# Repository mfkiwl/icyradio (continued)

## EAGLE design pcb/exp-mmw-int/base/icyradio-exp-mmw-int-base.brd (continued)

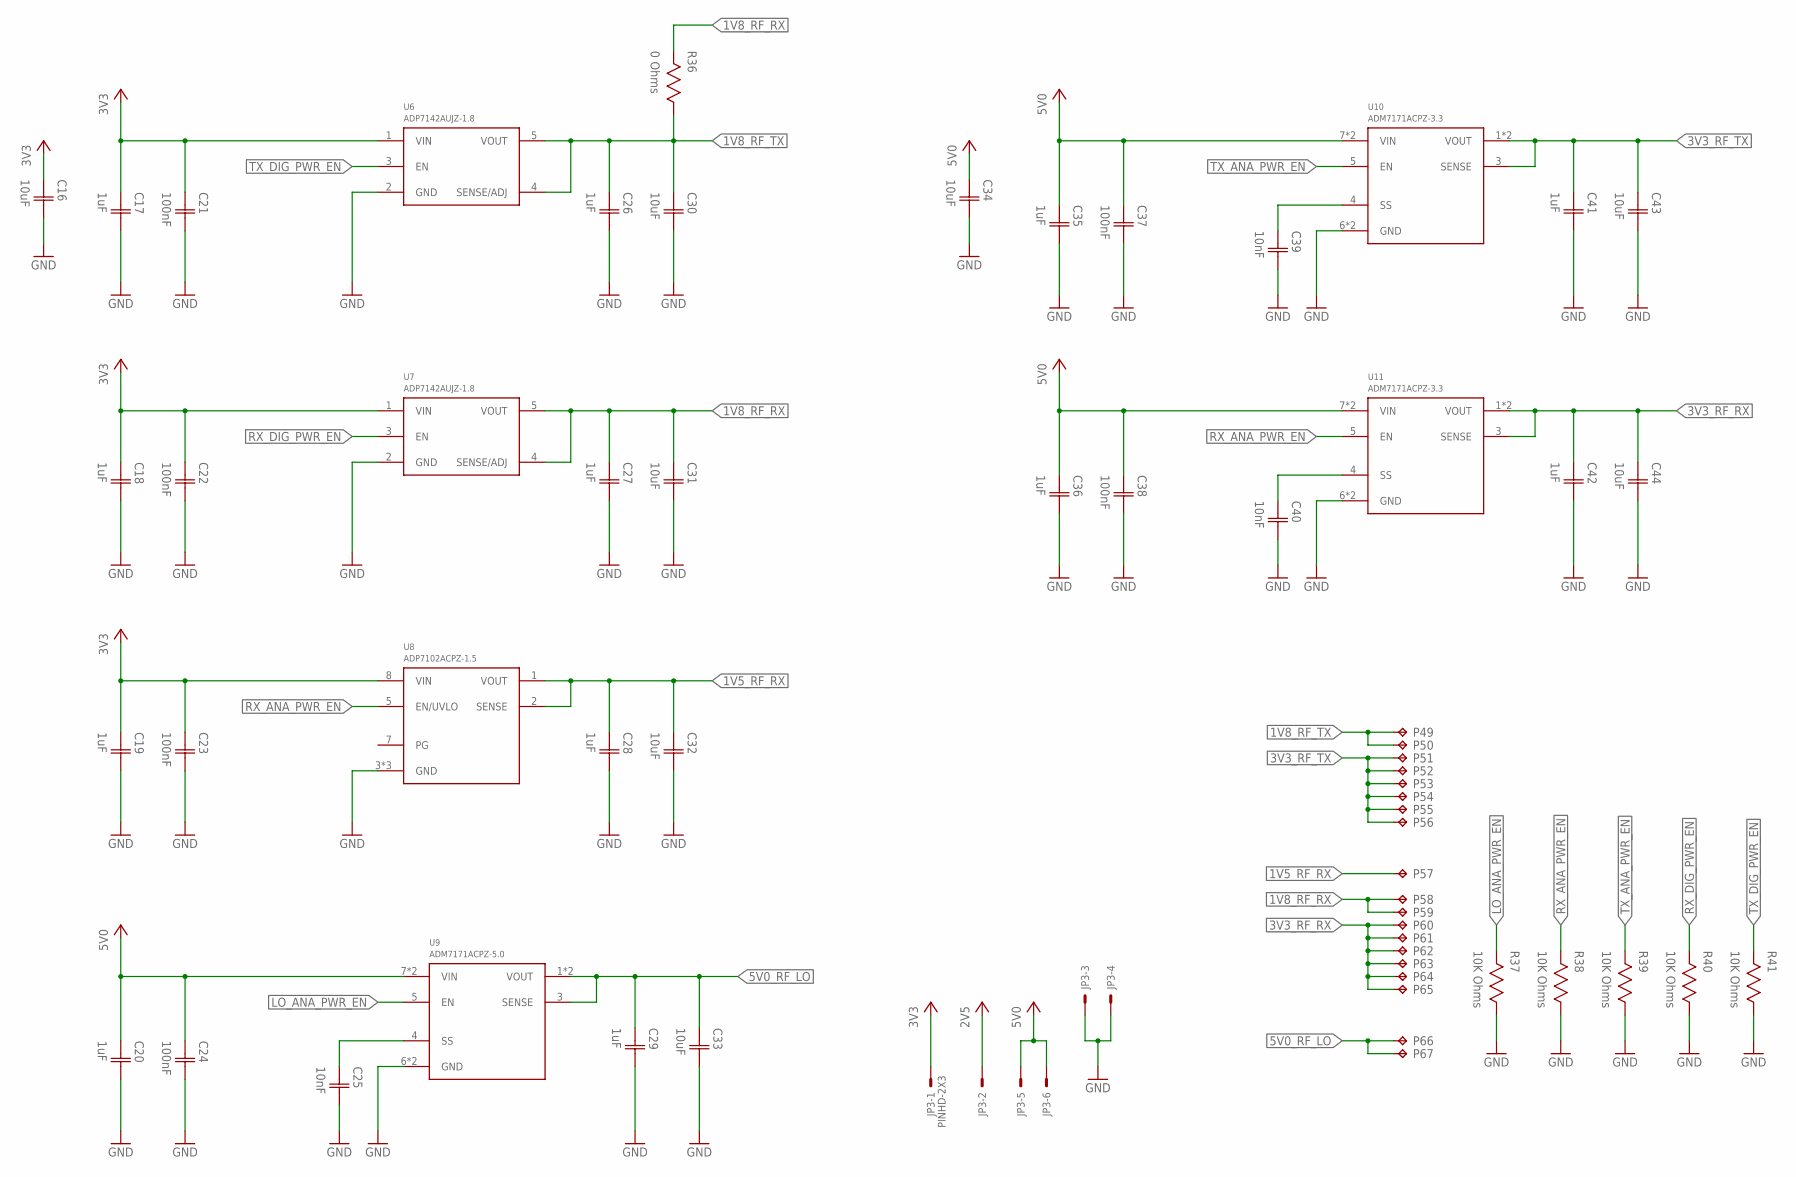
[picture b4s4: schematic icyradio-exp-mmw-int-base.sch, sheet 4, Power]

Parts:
C16, C34: 10uF; CAP0603
C17, C18, C19, C20, C26, C27, C28, C29, C35, C36, C41, C42: 1uF; CAP0402
C21, C22, C23, C24, C37, C38: 100nF; CAP0402
C25, C39, C40: 10nF; CAP0402
C30, C31, C32, C33, C43, C44: 10uF; CAP0402
JP3: PINHD-2X3; 2X03
P49, P50, P51, P52, P53, P54, P55, P56, P57, P58, P59, P60, P61, P62, P63, P64, P65, P66, P67: CHOLE-0.9MM-LAND; CAST_HOLE_0P9MM_LAND
R36: 0 Ohms; RES0402
R37, R38, R39, R40, R41: 10K Ohms; RES0402
U6, U7: ADP7142AUJZ-1.8; SOT23-5
U8: ADP7102ACPZ-1.5; LFCSP8_3X3
U9: ADM7171ACPZ-5.0; LFCSP8_3X3
U10, U11: ADM7171ACPZ-3.3; LFCSP8_3X3

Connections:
1V5_RF_RX: C28.1 (C1), C32.1 (C1), P57.PAD_T, U8.1 (VOUT), U8.2 (SENSE)
1V8_RF_RX: C27.1 (C1), C31.1 (C1), P58.PAD_T, P59.PAD_T, R36.2, U7.4 (SENSE/ADJ), U7.5 (VOUT); also elsewhere on the board
1V8_RF_TX: C26.1 (C1), C30.1 (C1), P49.PAD_T, P50.PAD_T, R36.1, U6.4 (SENSE/ADJ), U6.5 (VOUT); also elsewhere on the board
2V5: JP3.2
3V3: C16.1 (C1), C17.1 (C1), C18.1 (C1), C19.1 (C1), C21.1 (C1), C22.1 (C1), C23.1 (C1), JP3.1, U6.1 (VIN), U7.1 (VIN), U8.8 (VIN); also elsewhere on the board
3V3_RF_RX: C42.1 (C1), C44.1 (C1), P60.PAD_T, P61.PAD_T, P62.PAD_T, P63.PAD_T, P64.PAD_T, P65.PAD_T, U11.1 (VOUT), U11.2 (VOUT), U11.3 (SENSE)
3V3_RF_TX: C41.1 (C1), C43.1 (C1), P51.PAD_T, P52.PAD_T, P53.PAD_T, P54.PAD_T, P55.PAD_T, P56.PAD_T, U10.1 (VOUT), U10.2 (VOUT), U10.3 (SENSE)
5V0: C20.1 (C1), C24.1 (C1), C34.1 (C1), C35.1 (C1), C36.1 (C1), C37.1 (C1), C38.1 (C1), JP3.5, JP3.6, U9.7 (VIN), U9.8 (VIN), U10.7 (VIN), U10.8 (VIN), U11.7 (VIN), U11.8 (VIN)
5V0_RF_LO: C29.1 (C1), C33.1 (C1), P66.PAD_T, P67.PAD_T, U9.1 (VOUT), U9.2 (VOUT), U9.3 (SENSE)
GND: C16.2 (C2), C17.2 (C2), C18.2 (C2), C19.2 (C2), C20.2 (C2), C21.2 (C2), C22.2 (C2), C23.2 (C2), C24.2 (C2), C25.2 (C2), C26.2 (C2), C27.2 (C2), C28.2 (C2), C29.2 (C2), C30.2 (C2), C31.2 (C2), C32.2 (C2), C33.2 (C2), C34.2 (C2), C35.2 (C2), C36.2 (C2), C37.2 (C2), C38.2 (C2), C39.2 (C2), C40.2 (C2), C41.2 (C2), C42.2 (C2), C43.2 (C2), C44.2 (C2), JP3.3, JP3.4, R37.1, R38.1, R39.1, R40.1, R41.1, U6.2 (GND), U7.2 (GND), U8.3 (GND), U8.6 (GND), U8.9 (GND), U9.6 (GND), U9.9 (GND), U10.6 (GND), U10.9 (GND), U11.6 (GND), U11.9 (GND); also elsewhere on the board
LO_ANA_PWR_EN: R37.2, U9.5 (EN); also elsewhere on the board
unnamed: C40.1 (C1), U11.4 (SS)
unnamed: C25.1 (C1), U9.4 (SS)
unnamed: C39.1 (C1), U10.4 (SS)
RX_ANA_PWR_EN: R38.2, U8.5 (EN/UVLO), U11.5 (EN); also elsewhere on the board
RX_DIG_PWR_EN: R40.2, U7.3 (EN); also elsewhere on the board
TX_ANA_PWR_EN: R39.2, U10.5 (EN); also elsewhere on the board
TX_DIG_PWR_EN: R41.2, U6.3 (EN); also elsewhere on the board

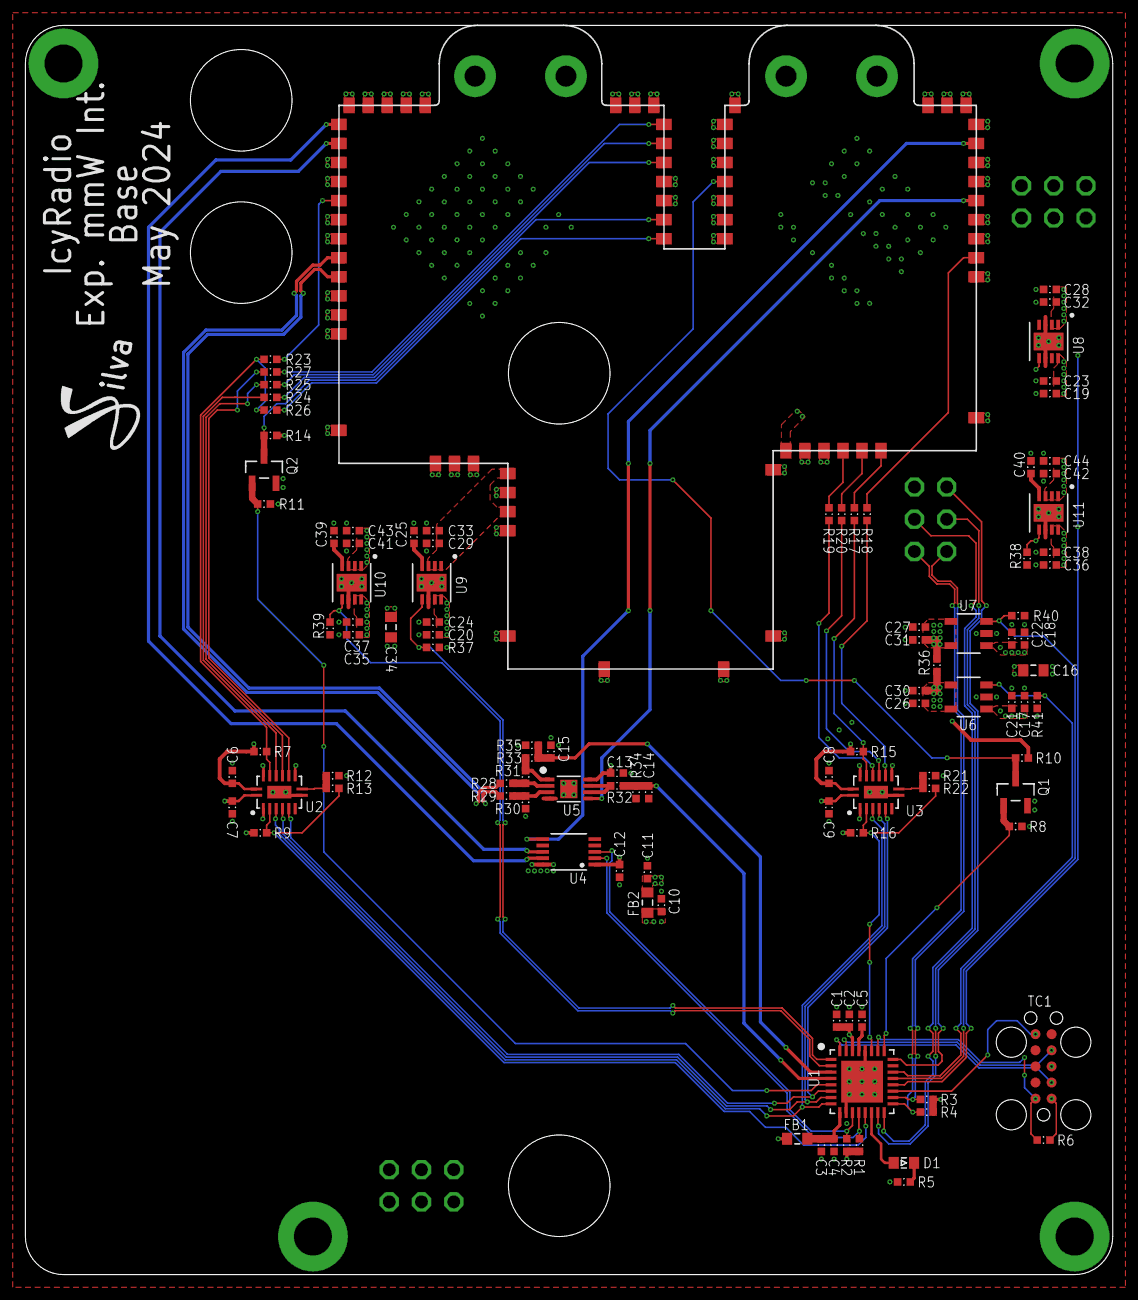
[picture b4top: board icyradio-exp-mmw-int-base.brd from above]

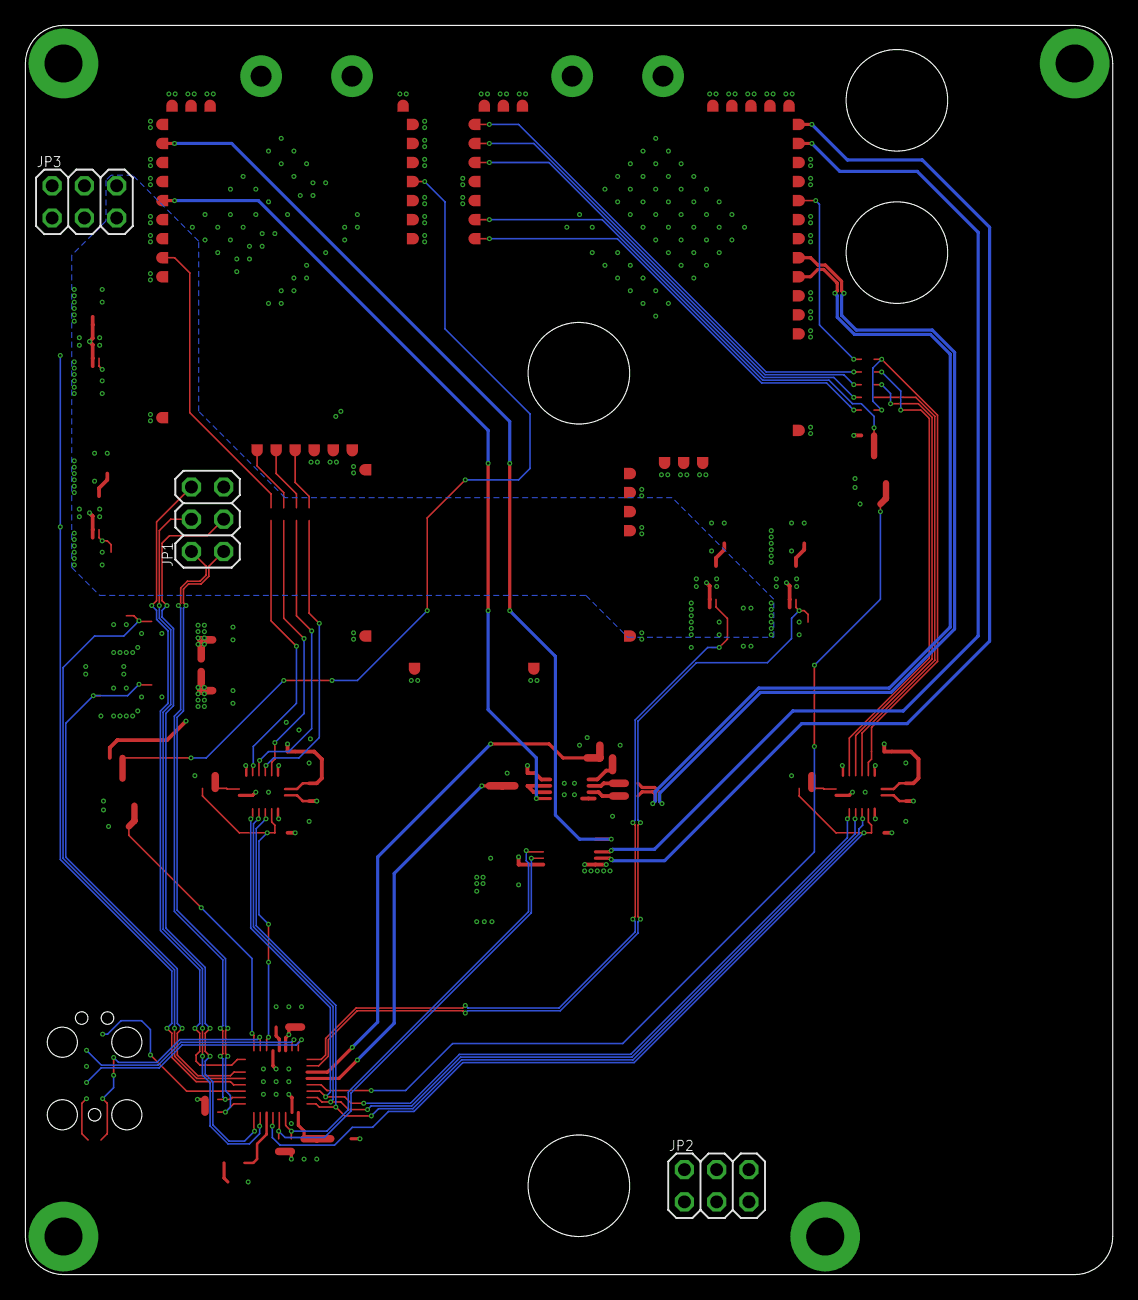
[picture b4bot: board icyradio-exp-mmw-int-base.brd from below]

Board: 4 copper layers, 85.7 x 98.4 mm, 173 parts (3 on the bottom side), 73 nets.

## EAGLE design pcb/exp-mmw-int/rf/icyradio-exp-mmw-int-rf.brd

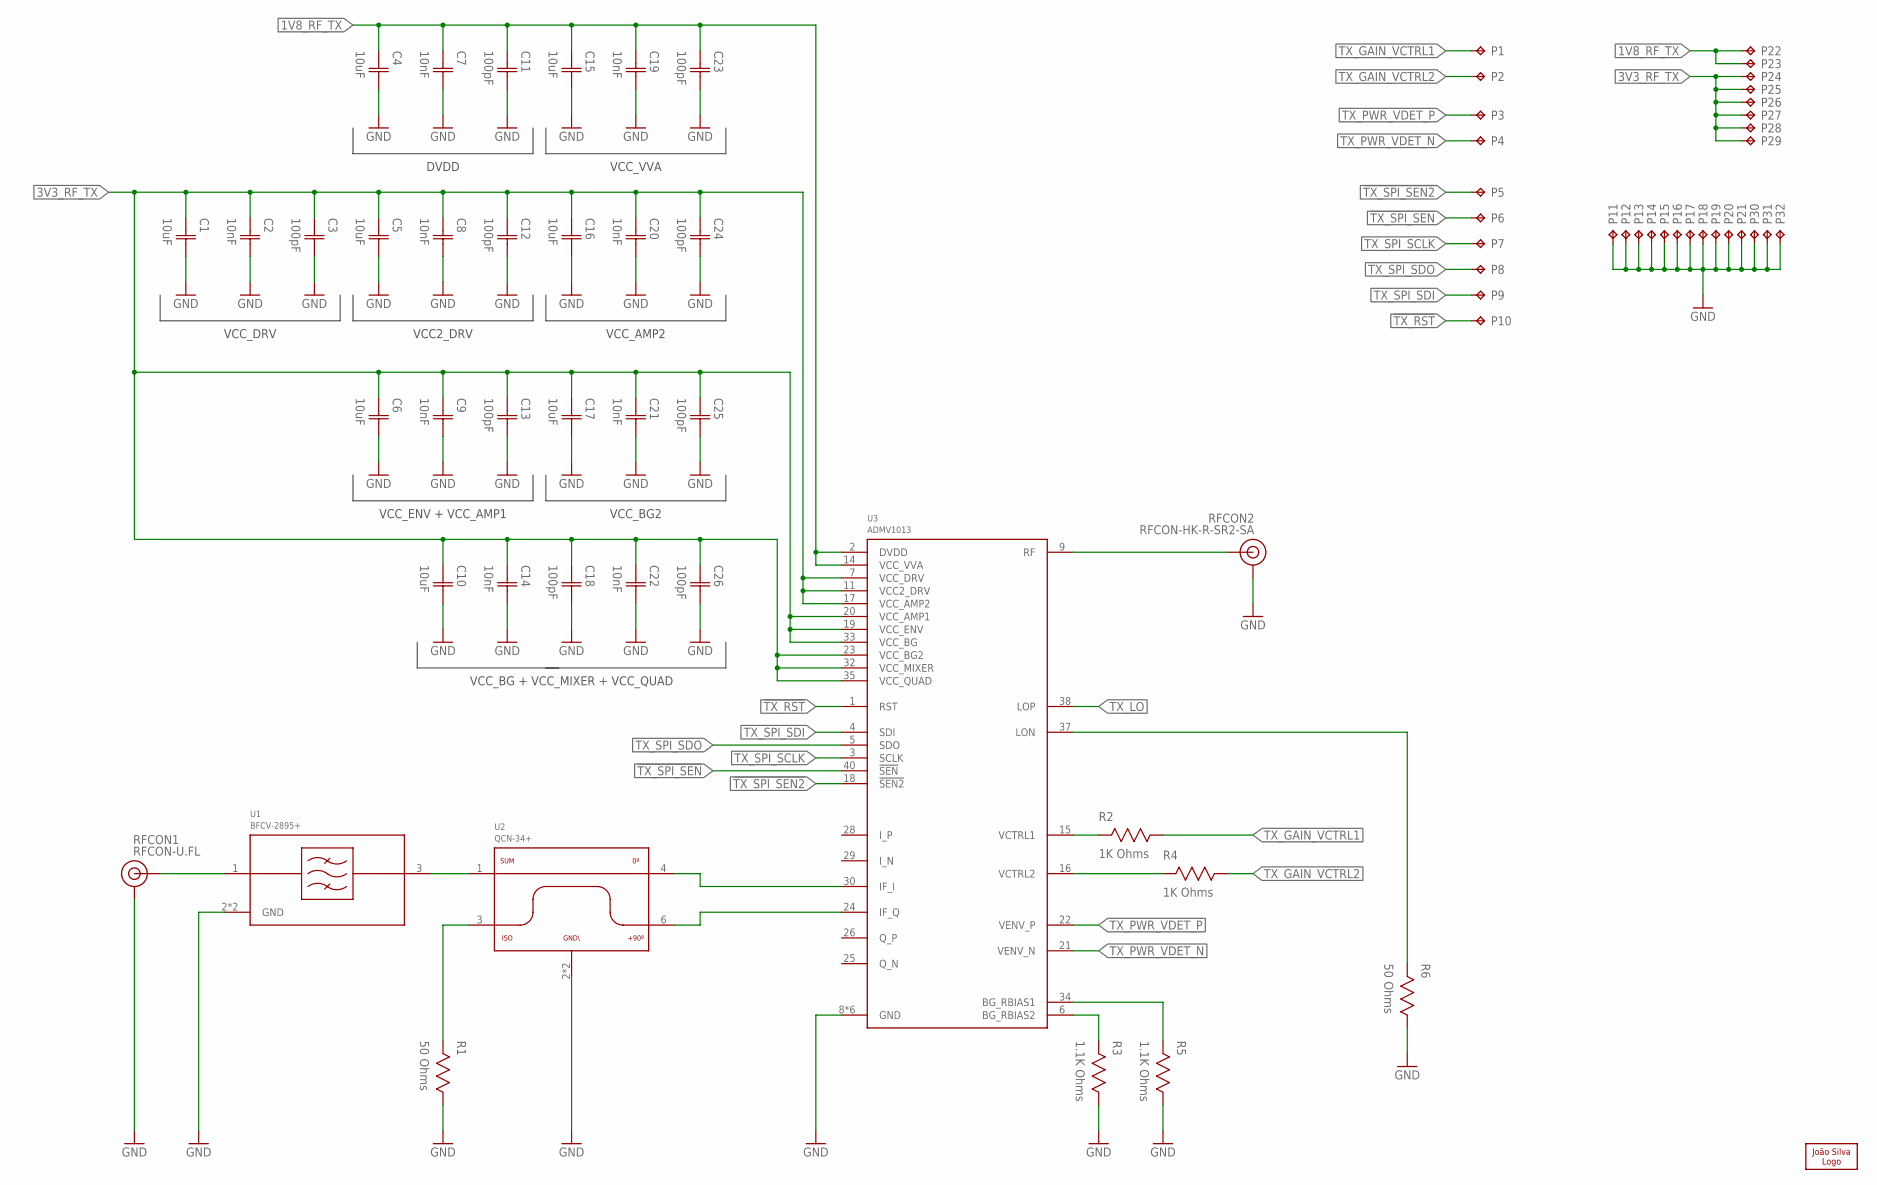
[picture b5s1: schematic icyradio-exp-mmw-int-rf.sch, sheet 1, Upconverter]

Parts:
C1, C4, C5, C6, C10, C15, C16, C17: 10uF; CAP0402
C2, C7, C8, C9, C14, C19, C20, C21, C22: 10nF; CAP0402
C3, C11, C12, C13, C18, C23, C24, C25, C26: 100pF; CAP0402
LOGO1: JSILVA-5MM; JSILVA_5MM
P1, P2, P3, P4, P5, P6, P7, P8, P9, P10, P22, P23, P24, P25, P26, P27, P28, P29: CHOLE-0.9MM-SS; CAST_HOLE_0P9MM_SS
P11, P12, P13, P14, P15, P16, P17, P18, P19, P20, P21, P30, P31, P32: CHOLE-0.9MM-DS; CAST_HOLE_0P9MM_DS
R1, R6: 50 Ohms; RES0402
R2, R4: 1K Ohms; RES0402
R3, R5: 1.1K Ohms; RES0402
RFCON1: RFCON-U.FL; U.FL
RFCON2: RFCON-HK-R-SR2-SA; HK-R-SR2-SA
U1: BFCV-2895+; JV1210C
U2: QCN-34+; FV1206-1
U3: ADMV1013; LGA40

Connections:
1V8_RF_TX: C4.1 (C1), C7.1 (C1), C11.1 (C1), C15.1 (C1), C19.1 (C1), C23.1 (C1), P22.PAD_T, P23.PAD_T, U3.2 (DVDD), U3.14 (VCC_VVA)
3V3_RF_TX: C1.1 (C1), C2.1 (C1), C3.1 (C1), C5.1 (C1), C6.1 (C1), C8.1 (C1), C9.1 (C1), C10.1 (C1), C12.1 (C1), C13.1 (C1), C14.1 (C1), C16.1 (C1), C17.1 (C1), C18.1 (C1), C20.1 (C1), C21.1 (C1), C22.1 (C1), C24.1 (C1), C25.1 (C1), C26.1 (C1), P24.PAD_T, P25.PAD_T, P26.PAD_T, P27.PAD_T, P28.PAD_T, P29.PAD_T, U3.7 (VCC_DRV), U3.11 (VCC2_DRV), U3.17 (VCC_AMP2), U3.19 (VCC_ENV), U3.20 (VCC_AMP1), U3.23 (VCC_BG2), U3.32 (VCC_MIXER), U3.33 (VCC_BG), U3.35 (VCC_QUAD)
!TX_RST: P10.PAD_T, U3.1 (RST)
!TX_SPI_SEN: P6.PAD_T, U3.40 (!SEN)
!TX_SPI_SEN2: P5.PAD_T, U3.18 (!SEN2)
GND: C1.2 (C2), C2.2 (C2), C3.2 (C2), C4.2 (C2), C5.2 (C2), C6.2 (C2), C7.2 (C2), C8.2 (C2), C9.2 (C2), C10.2 (C2), C11.2 (C2), C12.2 (C2), C13.2 (C2), C14.2 (C2), C15.2 (C2), C16.2 (C2), C17.2 (C2), C18.2 (C2), C19.2 (C2), C20.2 (C2), C21.2 (C2), C22.2 (C2), C23.2 (C2), C24.2 (C2), C25.2 (C2), C26.2 (C2), P11.PAD_B, P11.PAD_T, P12.PAD_B, P12.PAD_T, P13.PAD_B, P13.PAD_T, P14.PAD_B, P14.PAD_T, P15.PAD_B, P15.PAD_T, P16.PAD_B, P16.PAD_T, P17.PAD_B, P17.PAD_T, P18.PAD_B, P18.PAD_T, P19.PAD_B, P19.PAD_T, P20.PAD_B, P20.PAD_T, P21.PAD_B, P21.PAD_T, P30.PAD_B, P30.PAD_T, P31.PAD_B, P31.PAD_T, P32.PAD_B, P32.PAD_T, R1.1, R3.1, R5.1, R6.1, RFCON1.P$1 (GND), RFCON1.P$2 (GND), RFCON2.GND@1 (GND), RFCON2.GND@2 (GND), U1.2 (GND), U1.4 (GND), U2.2 (GND), U2.5 (GND), U3.8 (GND), U3.10 (GND), U3.27 (GND), U3.36 (GND), U3.39 (GND), U3.41 (GND); also elsewhere on the board
unnamed: R3.2, U3.6 (BG_RBIAS2)
unnamed: R5.2, U3.34 (BG_RBIAS1)
unnamed: R1.2, U2.3 (ISO)
unnamed: R2.2, U3.15 (VCTRL1)
unnamed: R4.2, U3.16 (VCTRL2)
TX_GAIN_VCTRL1: P1.PAD_T, R2.1
TX_GAIN_VCTRL2: P2.PAD_T, R4.1
TX_IF_FILT: U1.3 (RFOUT), U2.1 (SUM)
TX_IF_I: U2.4 (0DEG), U3.30 (IF_I)
TX_IF_IN: RFCON1.P$3 (SIGNAL), U1.1 (RFIN)
TX_IF_Q: U2.6 (P90DEG), U3.24 (IF_Q)
TX_LO: U3.38 (LOP); also elsewhere on the board
TX_LO_N: R6.2, U3.37 (LON)
TX_PWR_VDET_N: P4.PAD_T, U3.21 (VENV_N)
TX_PWR_VDET_P: P3.PAD_T, U3.22 (VENV_P)
TX_RF: RFCON2.SIG (SIGNAL), U3.9 (RF)
TX_SPI_SCLK: P7.PAD_T, U3.3 (SCLK)
TX_SPI_SDI: P9.PAD_T, U3.4 (SDI)
TX_SPI_SDO: P8.PAD_T, U3.5 (SDO)

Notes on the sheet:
DVDD
VCC_VVA
VCC2_DRV
VCC_AMP2
VCC_DRV
VCC_BG2
VCC_ENV + VCC_AMP1
VCC_BG + VCC_MIXER + VCC_QUAD

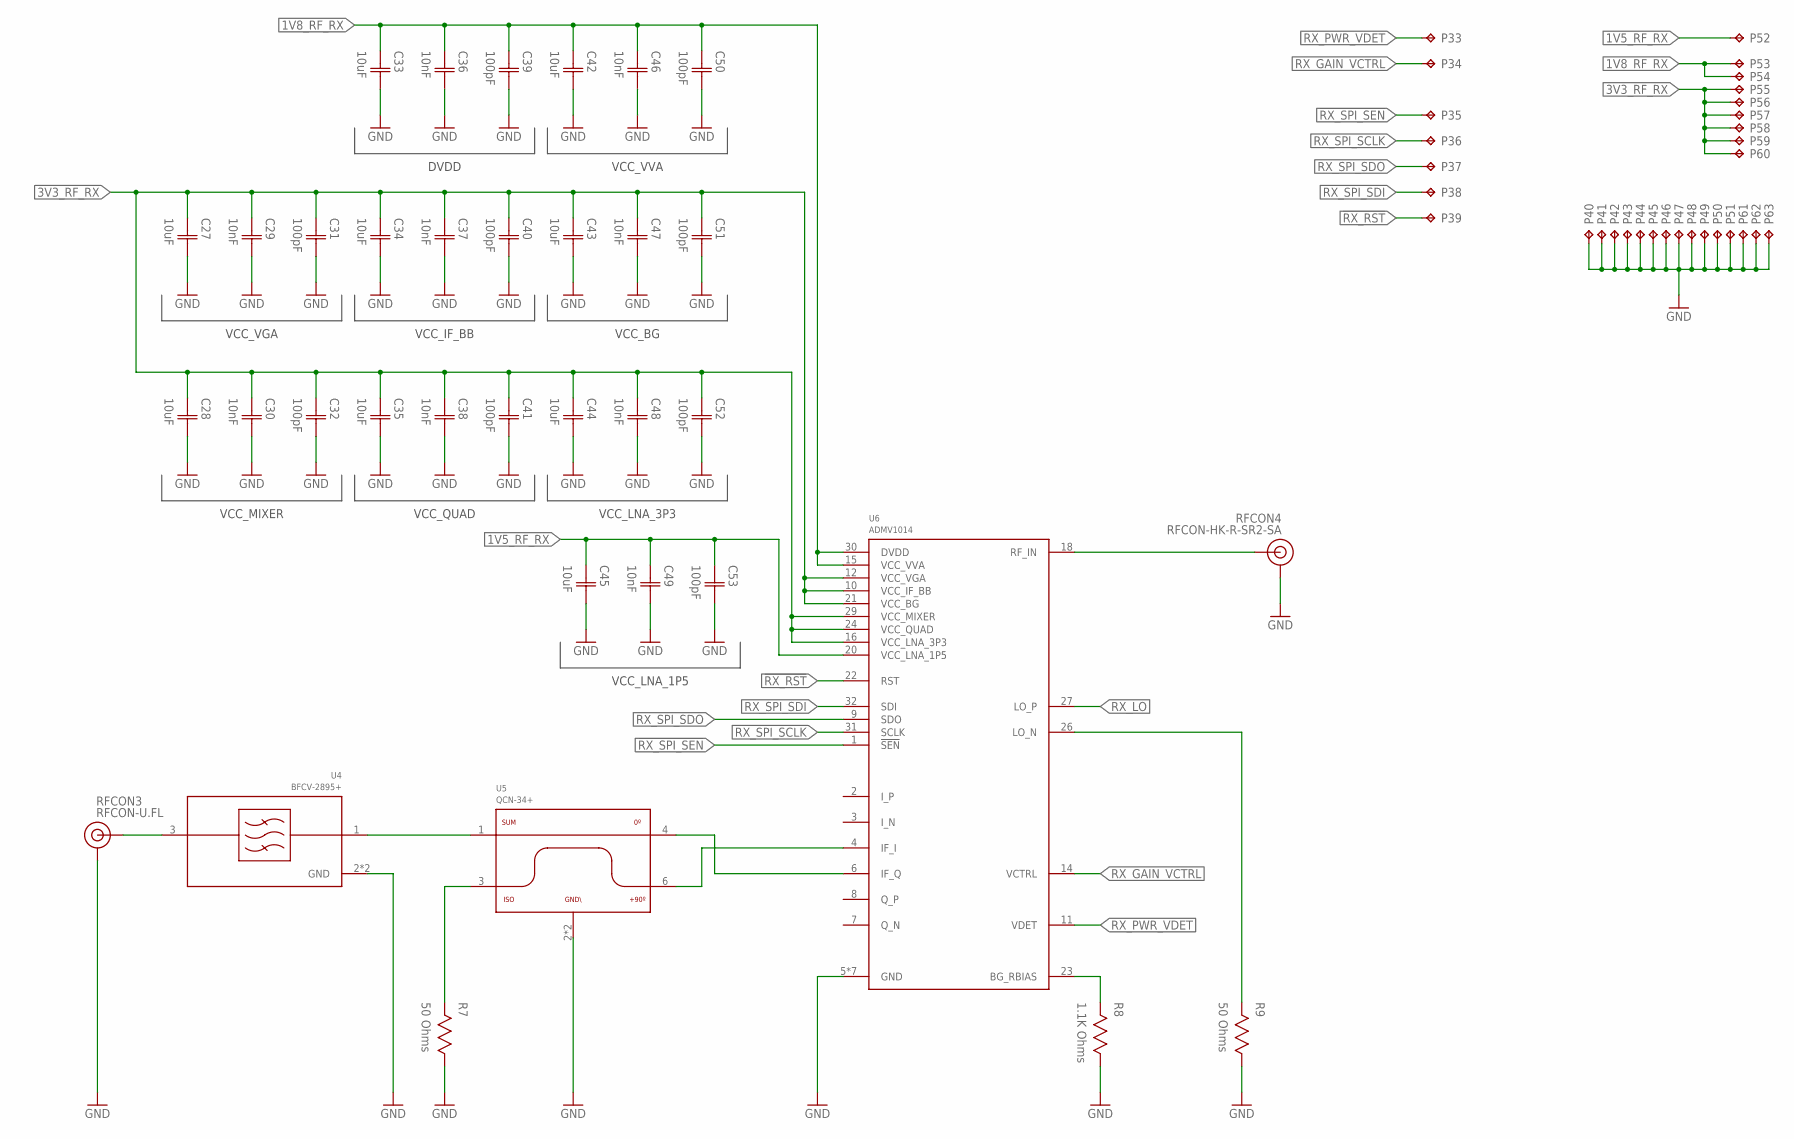
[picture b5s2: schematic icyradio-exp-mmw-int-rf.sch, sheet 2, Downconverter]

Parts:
C27, C28, C33, C34, C35, C42, C43, C44, C45: 10uF; CAP0402
C29, C30, C36, C37, C38, C46, C47, C48, C49: 10nF; CAP0402
C31, C32, C39, C40, C41, C50, C51, C52, C53: 100pF; CAP0402
P33, P34, P35, P36, P37, P38, P39, P52, P53, P54, P55, P56, P57, P58, P59, P60: CHOLE-0.9MM-SS; CAST_HOLE_0P9MM_SS
P40, P41, P42, P43, P44, P45, P46, P47, P48, P49, P50, P51, P61, P62, P63: CHOLE-0.9MM-DS; CAST_HOLE_0P9MM_DS
R7, R9: 50 Ohms; RES0402
R8: 1.1K Ohms; RES0402
RFCON3: RFCON-U.FL; U.FL
RFCON4: RFCON-HK-R-SR2-SA; HK-R-SR2-SA
U4: BFCV-2895+; JV1210C
U5: QCN-34+; FV1206-1
U6: ADMV1014; LGA32

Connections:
1V5_RF_RX: C45.1 (C1), C49.1 (C1), C53.1 (C1), P52.PAD_T, U6.20 (VCC_LNA_1P5)
1V8_RF_RX: C33.1 (C1), C36.1 (C1), C39.1 (C1), C42.1 (C1), C46.1 (C1), C50.1 (C1), P53.PAD_T, P54.PAD_T, U6.15 (VCC_VVA), U6.30 (DVDD)
3V3_RF_RX: C27.1 (C1), C28.1 (C1), C29.1 (C1), C30.1 (C1), C31.1 (C1), C32.1 (C1), C34.1 (C1), C35.1 (C1), C37.1 (C1), C38.1 (C1), C40.1 (C1), C41.1 (C1), C43.1 (C1), C44.1 (C1), C47.1 (C1), C48.1 (C1), C51.1 (C1), C52.1 (C1), P55.PAD_T, P56.PAD_T, P57.PAD_T, P58.PAD_T, P59.PAD_T, P60.PAD_T, U6.10 (VCC_IF_BB), U6.12 (VCC_VGA), U6.16 (VCC_LNA_3P3), U6.21 (VCC_BG), U6.24 (VCC_QUAD), U6.29 (VCC_MIXER)
!RX_RST: P39.PAD_T, U6.22 (RST)
!RX_SPI_SEN: P35.PAD_T, U6.1 (!SEN)
GND: C27.2 (C2), C28.2 (C2), C29.2 (C2), C30.2 (C2), C31.2 (C2), C32.2 (C2), C33.2 (C2), C34.2 (C2), C35.2 (C2), C36.2 (C2), C37.2 (C2), C38.2 (C2), C39.2 (C2), C40.2 (C2), C41.2 (C2), C42.2 (C2), C43.2 (C2), C44.2 (C2), C45.2 (C2), C46.2 (C2), C47.2 (C2), C48.2 (C2), C49.2 (C2), C50.2 (C2), C51.2 (C2), C52.2 (C2), C53.2 (C2), P40.PAD_B, P40.PAD_T, P41.PAD_B, P41.PAD_T, P42.PAD_B, P42.PAD_T, P43.PAD_B, P43.PAD_T, P44.PAD_B, P44.PAD_T, P45.PAD_B, P45.PAD_T, P46.PAD_B, P46.PAD_T, P47.PAD_B, P47.PAD_T, P48.PAD_B, P48.PAD_T, P49.PAD_B, P49.PAD_T, P50.PAD_B, P50.PAD_T, P51.PAD_B, P51.PAD_T, P61.PAD_B, P61.PAD_T, P62.PAD_B, P62.PAD_T, P63.PAD_B, P63.PAD_T, R7.1, R8.1, R9.1, RFCON3.P$1 (GND), RFCON3.P$2 (GND), RFCON4.GND@1 (GND), RFCON4.GND@2 (GND), U4.2 (GND), U4.4 (GND), U5.2 (GND), U5.5 (GND), U6.5 (GND), U6.13 (GND), U6.17 (GND), U6.19 (GND), U6.25 (GND), U6.28 (GND), U6.33 (GND); also elsewhere on the board
unnamed: R8.2, U6.23 (BG_RBIAS)
unnamed: R7.2, U5.3 (ISO)
RX_GAIN_VCTRL: P34.PAD_T, U6.14 (VCTRL)
RX_IF: U4.1 (RFIN), U5.1 (SUM)
RX_IF_FILT: RFCON3.P$3 (SIGNAL), U4.3 (RFOUT)
RX_IF_I: U5.6 (P90DEG), U6.4 (IF_I)
RX_IF_Q: U5.4 (0DEG), U6.6 (IF_Q)
RX_LO: U6.27 (LO_P); also elsewhere on the board
RX_LO_N: R9.2, U6.26 (LO_N)
RX_PWR_VDET: P33.PAD_T, U6.11 (VDET)
RX_RF: RFCON4.SIG (SIGNAL), U6.18 (RF_IN)
RX_SPI_SCLK: P36.PAD_T, U6.31 (SCLK)
RX_SPI_SDI: P38.PAD_T, U6.32 (SDI)
RX_SPI_SDO: P37.PAD_T, U6.9 (SDO)

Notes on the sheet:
DVDD
VCC_VVA
VCC_BG
VCC_VGA
VCC_IF_BB
VCC_LNA_3P3
VCC_QUAD
VCC_LNA_1P5
VCC_MIXER

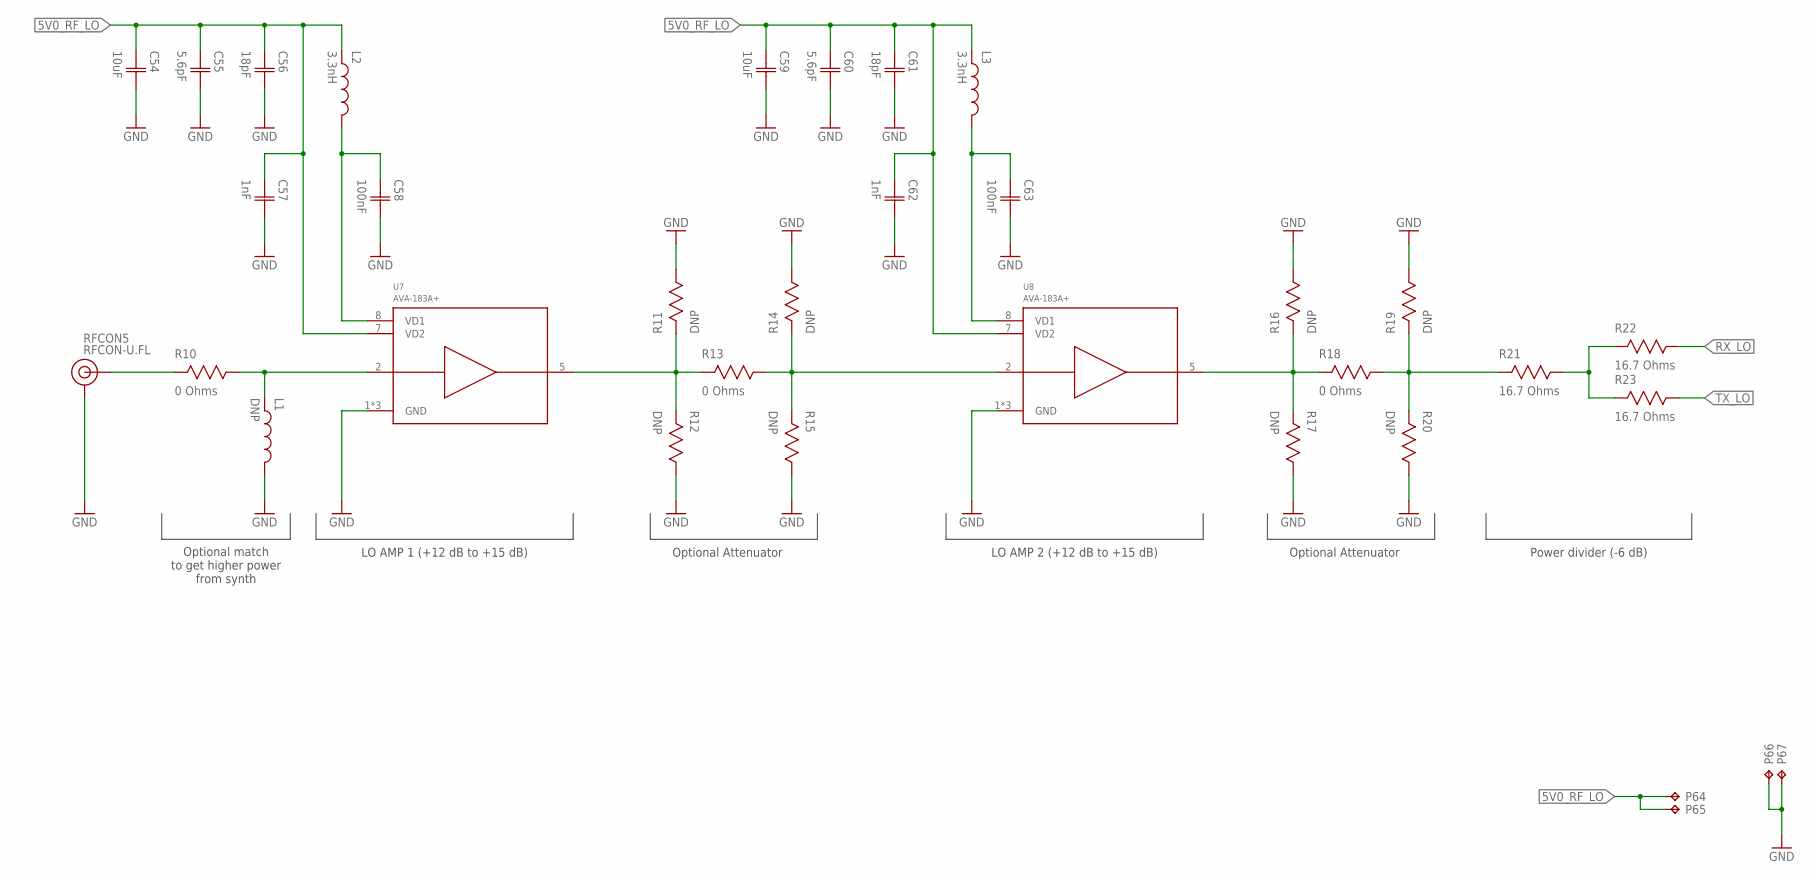
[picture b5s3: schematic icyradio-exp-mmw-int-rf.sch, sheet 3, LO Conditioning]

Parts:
C54, C59: 10uF; CAP0402
C55, C60: 5.6pF; CAP0402
C56, C61: 18pF; CAP0402
C57, C62: 1nF; CAP0402
C58, C63: 100nF; CAP0402
L1: DNP; IND0402
L2, L3: 3.3nH; IND0402
P64, P65: CHOLE-0.9MM-SS; CAST_HOLE_0P9MM_SS
P66, P67: CHOLE-0.9MM-DS; CAST_HOLE_0P9MM_DS
R10, R13, R18: 0 Ohms; RES0402
R11, R12, R14, R15, R16, R17, R19, R20: DNP; RES0402
R21, R22, R23: 16.7 Ohms; RES0402
RFCON5: RFCON-U.FL; U.FL
U7, U8: AVA-183A+; DQ849

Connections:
5V0_RF_LO: C54.1 (C1), C55.1 (C1), C56.1 (C1), C57.1 (C1), C59.1 (C1), C60.1 (C1), C61.1 (C1), C62.1 (C1), L2.1, L3.1, P64.PAD_T, P65.PAD_T, U7.7 (VD2), U8.7 (VD2)
GND: C54.2 (C2), C55.2 (C2), C56.2 (C2), C57.2 (C2), C58.2 (C2), C59.2 (C2), C60.2 (C2), C61.2 (C2), C62.2 (C2), C63.2 (C2), L1.2, P66.PAD_B, P66.PAD_T, P67.PAD_B, P67.PAD_T, R11.1, R12.1, R14.1, R15.1, R16.1, R17.1, R19.1, R20.1, RFCON5.P$1 (GND), RFCON5.P$2 (GND), U7.1 (GND), U7.6 (GND), U7.9 (GND), U8.1 (GND), U8.6 (GND), U8.9 (GND); also elsewhere on the board
LO_AMP1_IN: L1.1, R10.1, U7.2 (RFIN)
LO_AMP1_OUT: R11.2, R12.2, R13.2, U7.5 (RFOUT)
LO_AMP2_IN: R13.1, R14.2, R15.2, U8.2 (RFIN)
LO_AMP2_OUT: R16.2, R17.2, R18.2, U8.5 (RFOUT)
LO_AMP_VD1: C58.1 (C1), L2.2, U7.8 (VD1)
LO_AMP_VD2: C63.1 (C1), L3.2, U8.8 (VD1)
LO_IN: R10.2, RFCON5.P$3 (SIGNAL)
LO_OUT: R18.1, R19.2, R20.2, R21.2
LO_SPLIT: R21.1, R22.2, R23.2
RX_LO: R22.1; also elsewhere on the board
TX_LO: R23.1; also elsewhere on the board

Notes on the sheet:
Optional Attenuator
LO AMP 1 (+12 dB to +15 dB)
LO AMP 2 (+12 dB to +15 dB)
Optional match to get higher power from synth
Power divider (-6 dB)

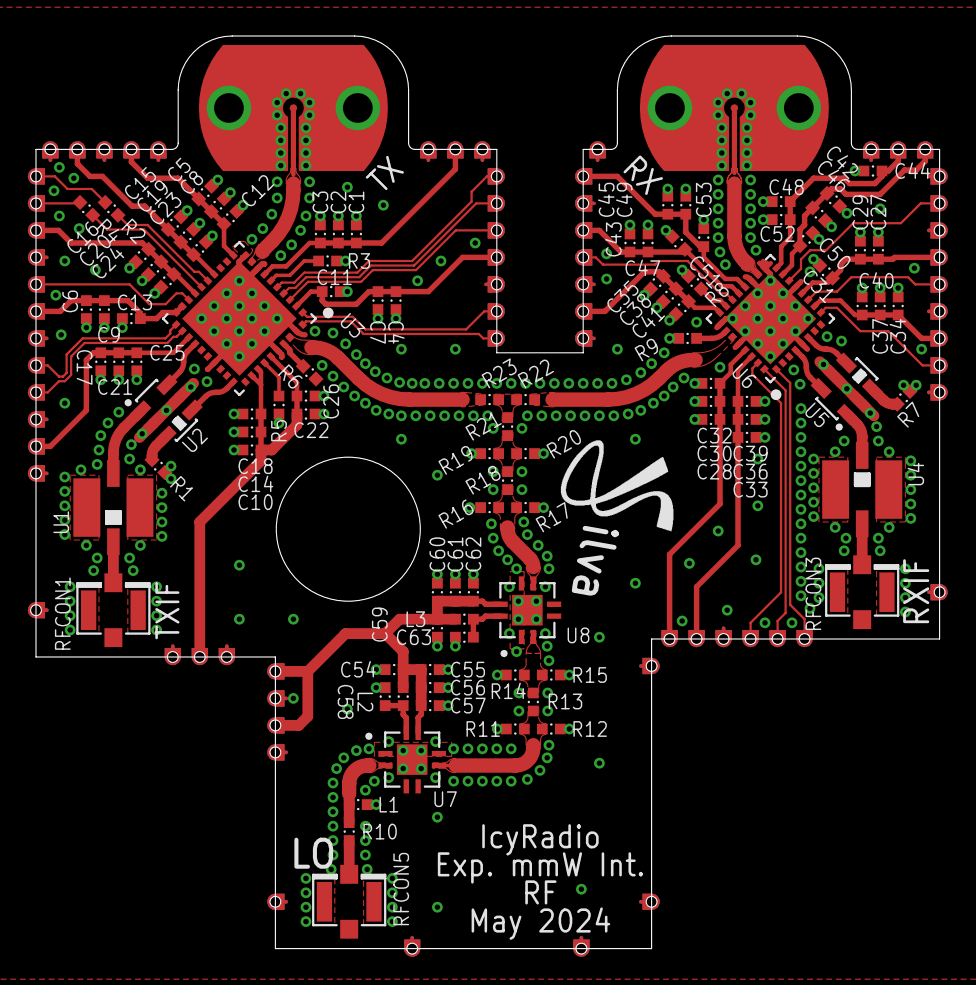
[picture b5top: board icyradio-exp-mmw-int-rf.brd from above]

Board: 2 copper layers, 50.2 x 50.7 mm, 170 parts (0 on the bottom side), 54 nets.

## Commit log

2024-04-06 Start working on mmWave expansion card
2024-04-06 HDL Work
2024-04-06 Add documentation
2024-04-06 driver: Use dma_mmap_coherent on all platforms
2024-04-06 soapy: Fix AD9361 error message soapy: Tune AD9361 to ISM band on startup soapy: Set AD9361 TX attenuation higher on startup soapy: Set AD9361 gain mode to manual on startup soapy: Round I2S clock di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
2024-04-24 soapy: Use 39 MHz as transceiver reference frequency to achieve integer division soapy: Use std::this_thread::sleep_for instead of usleep soapy: Allow 122.88 MSPS overclock sampling soapy: Add loop f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
2024-04-24 pcb: Update 3V3 switching regulator inductor to 4.7 uH so it exits DCM pcb: Update transceiver clock DC-block capacitor to 100nF
2024-04-24 driver: Add DKMS make target
2024-04-24 pmc: Dummy ADC read on startup pmc: Disable floating point ADC read functions at compile time pmc: Fix signed/unsigned integer temperature compensation pmc: Remove floating point math from SERCOM fun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
2024-05-28 firmware: Add Artix 200T project
2024-05-30 Add icyradio-apps repository URL
2024-05-30 pcb: Change mmWave Synth loop filter component values
2024-05-30 pcb: Finish mmWave integrated expansion PCBs for production
2024-05-30 exp/mmw-int: Add firmware
2024-05-30 pmc: Prepare LT7182S library conversion to fixed point pmc: Add fault log management methods (WIP) pmc: Fix unsigned temperature measurement errors pmc: Add debugger presence check pmc: Fix ID typo p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
2024-05-30 exp/template: Copy framework changes from pmc (check previous commits) exp/template: Completely remove floating-point math
2024-05-30 soapy: Explicitly set debug and release build flags soapy: Implement AD9361 gain mode switch methods soapy: Implement AD9361 RSSI readout methods soapy: Implement AD9361 FIR configuration methods soa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
2024-05-30 workflows: Build MCU firmwares in release mode Fix typo templace -> template
2024-06-01 pmc: Completely remove floating point math
2024-06-01 driver: Support multiple DMA buffers driver: Change ioctl calls
2024-06-01 soapy: Use std functions in LT7182S soapy: Check DDR3 init and calibration soapy: Use new ioctl numbers soapy: Start new DMA buffer management implementation soapy: Move utility functions soapy: Misc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
2024-06-05 Update github workflows to assess warnings
2024-06-05 exp-mmw: Work on software
2024-06-06 driver: Use correct DMA flags
2024-06-10 cli: Remove old CLI tool, replaced by IcyRadioTool included in the soapy build
2024-06-10 rv: Add PicoRV32 initial firmware environment
2024-06-11 Update armmem on embedded targets to elfmem
2024-07-20 pcb: Update TCXO AC couple capacitor to 100nF
2024-07-20 soapy: Use transceiver FIRs even when sample rate within supported range soapy: Fix auto PA switching
2024-07-20 docs: Update block diagrams
2024-10-08 pcb: Sync mmWave daughter card updates
2024-11-01 hdl: Sync HDL project changes
2024-11-10 hdl: Ignore FPGA binaries folder
2024-11-10 soapy: AXI IIC driver changes soapy: Only change what's needed
2024-11-10 hdl: Decrease drive strength
2024-11-10 pcb: Minor mmWave board schematic changes
2024-11-18 pcb: Update schematic PDF exp-mmw-int: Update software for new MCU (WIP)
2024-11-18 git: Update integrated mmWave expansion card build script
2024-11-18 git: Fix typo
2024-11-23 hdl: Update SPI and I2S cores
2024-11-23 soapy: Update drivers for new SPI core
2025-08-03 Add new 8V97003 datasheet Add cooling fan expansion card (WIP) Updated some schematic resistors from 49.9R to 50R Sync mmWave expansion card firmware after some lab testing (WIP) Sync PMC firmware Sy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
2025-08-03 Make soapy lib compatible with GCC 13.3.0
